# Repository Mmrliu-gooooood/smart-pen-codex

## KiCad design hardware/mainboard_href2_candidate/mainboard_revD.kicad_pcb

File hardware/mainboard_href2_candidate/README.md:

# HREF2: complete HREF continuity research — NOFAB, PI optimization still required

2026-10-28 UTC. This successor completes U101.23 ↔ U202.6 ↔ R220.1 continuity, but is **not preferred for manufacture merely because two connections remain**. Frozen HREF3 and BIAS4 are unchanged.

## Native result

Fresh ERC 0. Full native DRC with all severities, all track errors, schematic parity and `--exit-code-violations` returns **5**: **2 unconnected items, 33 dangling-via warnings, 3 dangling-track warnings and 16 missing-footprint parity issues**. Other native geometry checks report zero. All 90 schematic entities / 374 pin endpoints and all 74 footprint pad geometries remain unchanged from HREF3. No component was hidden to improve counts.

The remaining MCU control path is **U101.50 GPIO44/U0RXD → U203.6 (2A1) → U203.11 (2B1) → SENS_TRIG_IN**, with R223 bias. The historical CAM_PWDN_UART_RX name does not mean the pin is proven to be the custom camera's PWDN. The current design requires this connection; unverified camera use does not authorize deleting it. UART test use remains camera-off-only. The other unresolved RF_SIP connection needs an actual RF matching/antenna/controlled-geometry design, not a random signal trace.

## Changed topology, not all-old-copper preservation

The exact geometry multiset retains 3247 HREF3 copper items, removes/replaces 81 and adds 199. The explicit delta includes local CAM_D7, CAM_VSYNC, CHIP_EN, GND and 3V3_AON changes derived from the older frontier research, plus new HREF routing and a relocated R220 ground connection. See the transplantation and new-net contracts in `reproduction`. It is incorrect to reuse HREF3's statement that every old copper item is retained.

All 27 AON, 75 GND and 11 VIO endpoints remain connected, as do the other previously connected multi-pad nets. Connectivity does not qualify current capacity, decoupling, EMI or waveform timing.

## Power and return qualifications remain open

C201 is still 100 nF X7R at its original pad location. Its 0.15 mm feed changes from 0.825 mm to 0.625 + 0.848528 = 1.473528 mm; the 0.6/0.3 mm AON via moves from (1,33.6) to (1.6,34) mm. Under a conditional 17 µm copper / 85°C calculation, resistance changes about 7.002→12.507 mΩ; a purely assumed 500 mA would add about 2.752 mV. This is not measured branch current, a decoupling-loop model or PI approval. The nearest GND via distance also increases from about 2.352 to 2.623 mm. Further local shortening and return optimization must be considered before selection.

The old roughly 0.2 mm / 5.15 mm SCL/SDA AON neck remains: the y51.7–56.8 mm sampled fill is unchanged, and the input-to-upper-bridge raster path still survives 0.1 mm erosion but not 0.125 mm. This research does not solve that bottleneck. Plane fill changes elsewhere, including near the new In2 HREF segment.

In2 HREF routing totals about 5.472792 mm. Independent ≤25 µm sampling found 40 of 224 centre points outside actual In1 GND, all within 0.450694 mm of the endpoint HREF vias: this is principally the vias' own antipad clearance, **not evidence of a long mid-route ground split**. The ±150 µm corridor has additional nearby signal-hole boundaries. The endpoint vias are about 1.409/1.531 mm from the nearest GND vias. Actual transition return impedance and waveforms remain unqualified; sample ratios are not failure probabilities.

## Evidence and reproducibility

The independent review is at `hardware/href2_independent_review_20261028/REVIEW.md`; the separate power study is at `hardware/power_href2_review/REVIEW.md`. The candidate's `guard_proof` tests good/wrong-net/empty/missing/duplicate contracts in normal and optimized Python. Bad cases must stop before DRC; good cases reach the actual expected incomplete-board DRC exit 5. Optimized generator output is compared by full copper geometry multiset, not UUID equality.

Reproduction depends on the explicitly identified XCLK5, HREF3 and earlier frontier research board hashes, as well as the existing fine-process contract. This directory is not a standalone manufacturing package. Failed shorting/clearance experiments in the sibling trial directory are not this result and must not be merged silently.

R220 remains the HREF3 B-side 0603 placement, so its back-side body, mask/stencil/nearby via and enclosure gates persist. Grid-derived staircase fragments still need deliberate cleanup after connectivity settles. USB/RF, physical interface ownership, battery/NTC/charging, camera levels/timing/optics, whole housing fit, cost and actual writing remain open. No charging bridge was closed, no physical test or purchase occurred, and no Gerbers were released.

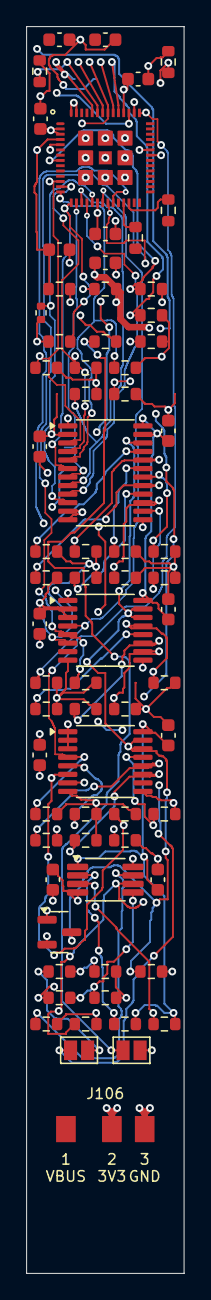
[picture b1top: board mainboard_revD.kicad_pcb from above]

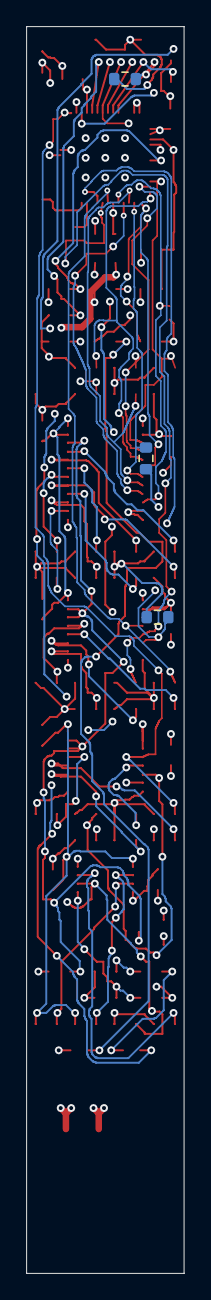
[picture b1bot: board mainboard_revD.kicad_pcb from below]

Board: 4 copper layers, 12.0 x 95.0 mm, 74 parts (3 on the bottom side), 54 nets.

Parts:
C101: 1u; C_0603_1608Metric
C102: 22u; C_0603_1608Metric
C103, C104, C105: 100n; C_0603_1608Metric
C106, C107: DNP RF_TUNE; C_0603_1608Metric
C201, C202, C203, C204, C205, C206, C207, C208: 100n X7R; C_0603_1608Metric
J106: POWER_CORE; PowerWireLands3_KeyGap_NOFAB
JP201: DNP_IO_COMMISSION; SolderJumper-2_P1.3mm_Open_Pad1.0x1.5mm
JP202: DNP_SCCB_COMMISSION; SolderJumper-2_P1.3mm_Open_Pad1.0x1.5mm
Q201: PMV30UN2; SOT-23
R101, R102, R103, R104, R105, R203, R206, R207: 10k 1%; R_0603_1608Metric
R106, R107, R108, R109, R202, R210, R211, R212, R213, R214, R215, R216, R218, R219, R220, R221, R222, R223, R224, R225, R226, R227, R228, R229, R230, R231, R232, R233, R234, R235, R237: 100k 1%; R_0603_1608Metric
R112, R113: 22R SI_TBD; R_0603_1608Metric
R201: 1k 1%; R_0603_1608Metric
R204: 100R 1%; R_0603_1608Metric
R205: 4.7k 1%; R_0603_1608Metric
R217: 100k 1%; R_0402_1005Metric
R236: 4.7k 1% RESET_CANDIDATE; R_0603_1608Metric
R240, R241, R242, R243: 10k 1% INITIAL_100kHz; R_0603_1608Metric
U101: ESP32-S3-PICO-1-N8R8; ESP32-S3-PICO-1_LGA57_7x7_P0.4_OfficialDerived_NOFAB
U201: SN74AXC8T245PWR; TSSOP-24_4.4x7.8mm_P0.65mm
U202, U203: SN74AXC4T245PWR; TSSOP-16_4.4x5mm_P0.65mm
U204: TCA9517DGKR; VSSOP-8_3x3mm_P0.65mm

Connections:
3V3_AON: C102.1, C103.1, C104.1, C105.1, C201.1, C203.1, C205.1, C207.1, J106.2, R101.2, R102.2, R103.2, R203.2, R240.2, R241.2, U101.2, U101.3, U101.20, U101.46, U101.55, U101.56, U201.1, U202.1, U203.1, U203.2, U203.3, U204.8
BOOT_N: R102.1, U101.5
CAM_BUS_EN: JP202.1, R108.1, U101.37
CAM_D0: R210.1, U101.12, U201.3
CAM_D1: R211.1, U101.13, U201.4
CAM_D2: R212.1, U101.14, U201.5
CAM_D3: R213.1, U101.15, U201.6
CAM_D4: R214.1, U101.16, U201.7
CAM_D5: R215.1, U101.17, U201.8
CAM_D6: R216.1, U101.18, U201.9
CAM_D7: R217.1, U101.19, U201.10
CAM_HREF: R220.1, U101.23, U202.6
CAM_IO_EN: JP201.1, R107.1, U101.48
CAM_ISO_OE_N: Q201.3, R203.1, U201.22, U202.14, U202.15, U203.14, U203.15
CAM_PCLK: R218.1, U101.21, U202.4
CAM_PWDN_UART_RX: R223.1, U101.50, U203.6
CAM_PWR_EN: R106.1, U101.47
CAM_RESET_UART_TX: R222.1, U101.49, U203.5
CAM_SCL: R240.1, U101.44, U204.7
CAM_SDA: R241.1, U101.45, U204.6
CAM_VSYNC: R219.1, U101.22, U202.5
CAM_XCLK: R221.1, U101.43, U203.4
CHIP_EN: C101.1, R101.1, U101.4
GND: C101.2, C102.2, C103.2, C104.2, C105.2, C106.2, C107.2, C201.2, C202.2, C203.2, C204.2, C205.2, C206.2, C207.2, C208.2, J106.3, Q201.2, R104.2, R105.2, R106.2, R107.2, R108.2, R109.2, R202.2, R205.2, R206.2, R207.2, R210.2, R211.2, R212.2, R213.2, R214.2, R215.2, R216.2, R217.2, R218.2, R219.2, R220.2, R221.2, R222.2, R223.2, R224.2, R225.2, R226.2, R227.2, R228.2, R229.2, R230.2, R231.2, R232.2, R233.2, R234.2, R235.2, R236.2, R237.2, U101.57, U201.2, U201.11, U201.12, U201.13, U202.2, U202.3, U202.8, U202.9, U203.8, U203.9, U204.4
ILLUM_STROBE: R109.1, U101.36
IO_ENABLE_LINK: JP201.2, R201.1
ISO_GATE: Q201.1, R201.2, R202.1
RF_SIP: C106.1, U101.1
SCCB_ENABLE_LINK: JP202.2, R204.1
SCCB_EN_SAFE: R204.2, R205.1, U204.5
SENS_D0: R224.1, U201.21
SENS_D1: R225.1, U201.20
SENS_D2: R226.1, U201.19
SENS_D3: R227.1, U201.18
SENS_D4: R228.1, U201.17
SENS_D5: R229.1, U201.16
SENS_D6: R230.1, U201.15
SENS_D7: R231.1, U201.14
SENS_EXTCLK: R235.1, U203.13
SENS_HREF: R234.1, U202.11
SENS_PCLK: R232.1, U202.13
SENS_SCL: R242.1, U204.2
SENS_SDA: R243.1, U204.3
SENS_TRIG_IN: R237.1, U203.11
SENS_VIO_1V8: C202.1, C204.1, C206.1, C208.1, R242.2, R243.2, U201.23, U201.24, U202.16, U203.16, U204.1
SENS_VSYNC: R233.1, U202.12
SENS_XSHUTDN_N: R236.1, U203.12
STRAP_GPIO3: R103.1, U101.8
STRAP_GPIO45: R104.1, U101.51
STRAP_GPIO46: R105.1, U101.52
UNUSED_A_INPUT: R207.1, U203.7
UNUSED_B_INPUT: R206.1, U202.10
USB_DM_MCU: R113.2, U101.25
USB_DP_MCU: R112.2, U101.26

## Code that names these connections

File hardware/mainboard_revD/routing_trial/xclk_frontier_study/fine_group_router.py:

#!/usr/bin/python3
"""Conservative local two-signal-layer grid search. Actual KiCad DRC is required afterwards."""
from pathlib import Path
import pcbnew as p,numpy as np,math,heapq,json,time,sys,os
D=Path(__file__).resolve().parent;STEP=.025;NX=481;NY=3801;TRACK_HALF=.127/2;EXTRA=.005
FINE=set(json.loads((D.parent/'fine_signal_process/fine_seed_v7_manifest.json').read_text())['fine_netclass_exact_names'])
def pair_clearance(other):return .127 if other in FINE else .15
def margin_to(other):return pair_clearance(other)+TRACK_HALF+EXTRA
source=sys.argv[1] if len(sys.argv)>1 else 'knownnets_commissioning'
outname=sys.argv[2] if len(sys.argv)>2 else 'knownnets_digital'
b=p.LoadBoard(str(D/(source+'.kicad_pcb')));layers=[p.F_Cu,p.B_Cu];results=[]
def xy(v):return(p.ToMM(v.x),p.ToMM(v.y))
def pt(a):return p.VECTOR2I(p.FromMM(float(a[0])),p.FromMM(float(a[1])))
def rectangle(arr,x,y,w,h,margin):
 x0=max(0,int(math.floor((x-w/2-margin)/STEP)));x1=min(NX,int(math.ceil((x+w/2+margin)/STEP))+1);y0=max(0,int(math.floor((y-h/2-margin)/STEP)));y1=min(NY,int(math.ceil((y+h/2+margin)/STEP))+1)
 xx=np.arange(x0,x1)[:,None]*STEP;yy=np.arange(y0,y1)[None,:]*STEP
 arr[x0:x1,y0:y1]|=(abs(xx-x)<=w/2+margin)&(abs(yy-y)<=h/2+margin)

def capsule(arr,a,z,r):
 x0=max(0,int(math.floor((min(a[0],z[0])-r)/STEP)));x1=min(NX,int(math.ceil((max(a[0],z[0])+r)/STEP))+1);y0=max(0,int(math.floor((min(a[1],z[1])-r)/STEP)));y1=min(NY,int(math.ceil((max(a[1],z[1])+r)/STEP))+1)
 if x1<=x0 or y1<=y0:return
 xx=np.arange(x0,x1)[:,None]*STEP;yy=np.arange(y0,y1)[None,:]*STEP;dx=z[0]-a[0];dy=z[1]-a[1];den=dx*dx+dy*dy
 u=np.clip(((xx-a[0])*dx+(yy-a[1])*dy)/den,0,1) if den>0 else 0
 arr[x0:x1,y0:y1]|=(xx-a[0]-u*dx)**2+(yy-a[1]-u*dy)**2<=r*r

def masks(net):
 assert net in FINE, 'This process router may only draw explicitly approved fine signal nets'
 obs=np.zeros((2,NX,NY),bool);vb=np.zeros((NX,NY),bool)
 obs[:,:math.ceil(.6/STEP),:]=True;obs[:,math.floor(11.4/STEP)+1:,:]=True;obs[:,:,:math.ceil(.6/STEP)]=True;obs[:,:,math.floor(94.4/STEP)+1:]=True
 vb[:math.ceil(.8/STEP),:]=True;vb[math.floor(11.2/STEP)+1:,:]=True;vb[:,:math.ceil(.8/STEP)]=True;vb[:,math.floor(94.2/STEP)+1:]=True
 for fp in b.GetFootprints():
  for a in fp.Pads():
   x,y=xy(a.GetPosition());w,h=xy(a.GetSize());angle=int(round(a.GetOrientationDegrees()))%180
   if angle==90:w,h=h,w
   for k,l in enumerate(layers):
    if a.IsOnLayer(l) and a.GetNetname()!=net:rectangle(obs[k],x,y,w,h,margin_to(a.GetNetname()))
   rectangle(vb,x,y,w,h,.3+.05 if a.GetNetname()==net else .3+pair_clearance(a.GetNetname())+.01) # no added via-in-pad, even own net
 for t in b.GetTracks():
  a=xy(t.GetStart());z=xy(t.GetEnd());other=t.GetNetname()!=net
  if isinstance(t,p.PCB_VIA):
   radius=p.ToMM(t.GetWidth(p.F_Cu))/2
   if other:
    for k in range(2):capsule(obs[k],a,a,radius+margin_to(t.GetNetname()))
   capsule(vb,a,a,.3+radius+pair_clearance(t.GetNetname())+.01 if other else .3+.25+.01)
  else:
   radius=p.ToMM(t.GetWidth())/2
   if t.GetLayer() in layers:
    if other:capsule(obs[layers.index(t.GetLayer())],a,z,radius+margin_to(t.GetNetname()))
   if other:capsule(vb,a,z,radius+.3+pair_clearance(t.GetNetname())+.01)
 # Reuse an already fabricated same-net via; no new drill there.
 for t in b.GetTracks():
  if isinstance(t,p.PCB_VIA) and t.GetNetname()==net:
   x,y=xy(t.GetPosition());ix=round(x/STEP);iy=round(y/STEP)
   if not obs[0,ix,iy] and not obs[1,ix,iy]:vb[ix,iy]=False
 return obs,vb

def search(a,z,obs,vb,ak=0,zk=0):
 start=(ak,round(a[0]/STEP),round(a[1]/STEP));goal=(zk,round(z[0]/STEP),round(z[1]/STEP))
 if obs[start] or obs[goal]:return None,'endpoint blocked'
 shape=(2,NX,NY);dist=np.full(shape,np.inf,dtype=np.float32);prev=np.full(shape,-1,dtype=np.int32);dist[start]=0
 def encode(k,x,y):return(k*NX+x)*NY+y
 def decode(v):y=v%NY;v//=NY;return(v//NX,v%NX,y)
 def h(x,y):dx=abs(x-goal[1]);dy=abs(y-goal[2]);return max(dx,dy)+.41421356*min(dx,dy)
 heap=[(h(start[1],start[2]),0,*start)];pops=0
 dirs=[(-1,0,1),(1,0,1),(0,-1,1),(0,1,1),(-1,-1,1.41421356),(-1,1,1.41421356),(1,-1,1.41421356),(1,1,1.41421356)]
 while heap:
  _,g,k,x,y=heapq.heappop(heap)
  if g>dist[k,x,y]+.001:continue
  pops+=1
  if (k,x,y)==goal:
   path=[];idx=encode(k,x,y)
   while idx!=-1:path.append(decode(idx));idx=int(prev[decode(idx)])
   return path[::-1],str(pops)
  if pops>2400000:return None,'search budget2400000 finergrid'
  for dx,dy,c in dirs:
   xx=x+dx;yy=y+dy
   if not(0<=xx<NX and 0<=yy<NY) or obs[k,xx,yy]:continue
   if dx and dy and (obs[k,x+dx,y] or obs[k,x,y+dy]):continue
   ng=g+c
   if ng+.001<dist[k,xx,yy]:dist[k,xx,yy]=ng;prev[k,xx,yy]=encode(k,x,y);heapq.heappush(heap,(ng+h(xx,yy),ng,k,xx,yy))
  kk=1-k
  if not vb[x,y] and not obs[kk,x,y]:
   ng=g+50
   if ng+.001<dist[kk,x,y]:dist[kk,x,y]=ng;prev[kk,x,y]=encode(k,x,y);heapq.heappush(heap,(ng+h(x,y),ng,kk,x,y))
 return None,'no path'

def add(net,path,a,z,ak=0,zk=0):
 points=[(k,x*STEP,y*STEP) for k,x,y in path];points=[(ak,*a)]+points+[(zk,*z)];segments=[]
 # Compress collinear grid sections, preserving layer switches.
 simple=[points[0]]
 for i in range(1,len(points)-1):
  q=points[i-1];v=points[i];w=points[i+1]
  if q[0]==v[0]==w[0] and abs((v[1]-q[1])*(w[2]-v[2])-(v[2]-q[2])*(w[1]-v[1]))<1e-8:continue
  simple.append(v)
 simple.append(points[-1])
 for q,v in zip(simple,simple[1:]):
  if q[0]!=v[0]:
   existing=any(isinstance(v,p.PCB_VIA) and v.GetNetname()==net and math.dist(xy(v.GetPosition()),q[1:])<1e-6 for v in b.GetTracks())
   if existing:continue
   via=p.PCB_VIA(b);via.SetPosition(pt(q[1:]));via.SetWidth(p.F_Cu,p.FromMM(.6));via.SetDrill(p.FromMM(.3));via.SetViaType(p.VIATYPE_THROUGH);via.SetLayerPair(p.F_Cu,p.B_Cu);via.SetNet(b.FindNet(net));b.Add(via)
  elif math.hypot(q[1]-v[1],q[2]-v[2])>1e-7:
   t=p.PCB_TRACK(b);t.SetStart(pt(q[1:]));t.SetEnd(pt(v[1:]));t.SetWidth(p.FromMM(.127));t.SetLayer(layers[q[0]]);t.SetNet(b.FindNet(net));b.Add(t)
 return len(simple)

def component(label):
 ref,pin=label.split('.')
 a=next(a for f in b.GetFootprints() if f.GetReference()==ref for a in f.Pads() if a.GetNumber()==pin)
 con=b.GetConnectivity();q=[a];seen=set();vias=[]
 while q:
  a=q.pop();key=a.m_Uuid.AsString()
  if key in seen:continue
  seen.add(key)
  if a.GetClass()=='PCB_VIA':vias.append(xy(a.GetPosition()))
  q.extend(con.GetConnectedTracks(a));q.extend(con.GetConnectedPads(a))
 return seen,vias
pads={}
for fp in b.GetFootprints():
 for a in fp.Pads():pads.setdefault(a.GetNetname(),[]).append((fp.GetReference()+'.'+a.GetNumber(),xy(a.GetPosition())))
skip={'GND','3V3_AON','RF_SIP','RF_ANT'}
priority=['ISO_GATE','SCCB_EN_SAFE','IO_ENABLE_LINK','SCCB_ENABLE_LINK','UNUSED_A_INPUT','UNUSED_B_INPUT','STRAP_GPIO3','STRAP_GPIO45','STRAP_GPIO46','CAM_IO_EN','CAM_PWR_EN','CAM_BUS_EN','ILLUM_STROBE','CAM_SCL','CAM_SDA','SENS_SCL','SENS_SDA']
if os.environ.get('IC_ONLY')=='1':pads={n:[a for a in aa if a[0].startswith('U')] for n,aa in pads.items()}
for net in pads:pads[net].sort(key=lambda a:(0 if a[0].startswith('U101.') else 1 if a[0].startswith('U2') else 2,a[0]))
selected=sys.argv[3].split(',') if len(sys.argv)>3 else priority
for net in selected:
 if net in skip or net not in pads or len(pads[net])<2:continue
 assert net in FINE, net
 remaining=pads[net][1:];connected=[pads[net][0]]
 while remaining:
  choices=[(math.dist(a[1],z[1]),a,z) for a in connected for z in remaining];_,a,z=min(choices)
  b.BuildConnectivity();ca,va=component(a[0]);cz,vz=component(z[0])
  if ca&cz:
   remaining.remove(z);connected.append(z);continue
  ap=min(va,key=lambda v:math.dist(v,z[1])) if va else a[1];zp=min(vz,key=lambda v:math.dist(v,ap)) if vz else z[1];ak=1 if va else 0;zk=1 if vz else 0
  obs,vb=masks(net);t0=time.time();path,why=search(ap,zp,obs,vb,ak,zk)
  result={'net':net,'from':a[0],'to':z[0],'success':path is not None,'actual_start':ap,'start_layer':ak,'actual_end':zp,'end_layer':zk,'search':why,'seconds':round(time.time()-t0,3)}
  if path:result['points']=add(net,path,ap,zp,ak,zk)
  print(result,flush=True);results.append(result);remaining.remove(z);connected.append(z)
 out=D/(outname+'.kicad_pcb');p.SaveBoard(str(out),b)
# Fill after readback; restoring project prevents SaveBoard resetting default .15mm rule.
out=D/(outname+'.kicad_pcb');p.SaveBoard(str(out),b);b=p.LoadBoard(str(out));p.ZONE_FILLER(b).Fill(b.Zones());p.SaveBoard(str(out),b);(D/(outname+'.kicad_pro')).write_text((D/(source+'.kicad_pro')).read_text());(D/(outname+'_search.json')).write_text(json.dumps(results,indent=2))

(D/(outname+'.kicad_dru')).write_text((D/(source+'.kicad_dru')).read_text())
